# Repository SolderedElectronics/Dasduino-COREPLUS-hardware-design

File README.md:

# Dasduino COREPLUS Hardware Design

## About the Product

|  |
| :----------------------------------------------------------: |
| [Buy Dasduino COREPLUS](https://www.solde.red/333268) |

The soldered version of the ATmega2560 microcontroller board has arrived! It is designed for enthusiasts and professionals in the field of electronics and DIY projects. The heart of the board, the ATmega2560, is a powerful 8-bit microcontroller that offers enough processing power for demanding applications. The board comes with a large number of digital and analog inputs/outputs, allowing users to connect various sensors and actuators. The ATmega2560 contains a significant amount of Flash memory, SRAM, and EEPROM, which is sufficient for complex applications and data storage. The USB interface allows for easy programming and communication with a computer. It enables communication with various peripheral devices and modules using the qwiic system for simple connectivity. The board is compatible with popular development environments, such as Arduino IDE, which facilitates the development and implementation of projects.

This board is ideal for creating complex and versatile electronic projects, such as automatic systems, smart devices, robotics, and many others.

---

## Repository Contents

This repository contains all design files for Dasduino COREPLUS, organized as follows:

- **`CAD` folder**: Contains KiCAD design files, including:
  - Schematics
  - PCB layout
  - Panel PCB layout
  - Source 3D files in Fusion360, if any
  - All files are sorted by version with a detailed change log.
- **`OUTPUTS` folder**: Includes all production-ready files, such as:
  - Bill of Materials (BOM) and interactive BOM (iBOM)
  - PDF versions of schematics
  - 3D `.step` file of the board
  - 3D-printable models
  - Gerber files for PCB manufacturing
  - Image of the pinout of the board
  - Product image
  - Compliance, legal and generic sales documents

Refer to the `Change Log` in the CAD folder for details about updates between versions.

---

## Learn More About the Product

Beyond the repository, explore the following resources:

### Soldered Verify

The **Soldered Verify** system ensures every board you purchase from Soldered is fully functional. It also provides access to exclusive test data for your product. To get started, find the unique Soldered Verify ID on your product's packaging and enter the ID on the [Soldered Verify page](https://soldered.com/verify/) to access test results and additional product details.

### Soldered Community

Soldered Community is your go-to place for technical support. Our engineers track and answer all questions posted there, and it’s a great space for the maker community. Get answers to your questions and solutions for your challenges at [Soldered Community](https://soldered.com/community).

### solde.red

solde.red is an ultimate URL shortener and information hub. Access it by typing solde.red/ followed by your product SKU, e.g., [solde.red/333000](https://solde.red/333000), to find getting-started guides, datasheets, open-source hardware and software files, certifications, images, pinouts, and more. Read more about the shortener [here](https://solde.red/info/).

---

## Contributing

Contributions are welcome! Here’s how you can get involved:

- Submit pull requests to enhance the design or fix issues.
- Report bugs or problems by opening an issue.

We encourage community collaboration to make this product even better.

---

## About Soldered

[Soldered for Makers](https://soldered.com) specializes in designing and manufacturing electronic products tailored for enthusiasts, ranging from hobbyists to professionals. Our portfolio includes electronic boards, sensors, and actuators that are widely utilized in fields such as microelectronics, mechatronics, robotics, programming, and IoT. Every product we offer is designed in-house and built upon open-source hardware and software platforms. Proudly certified and manufactured within the European Union, our catalog likely includes the product you need for your project.

We complement these products with comprehensive tutorials and manuals, product descriptions, schematics, programming codes, and project examples. Our round-the-clock [customer and technical support](https://soldered.com/community) is available for all our products, irrespective of the sales channel. Soldered’s success and services reflect our maker community’s unwavering [trust](https://www.trustpilot.com/review/soldered.com), for which we are deeply grateful. Join our community and create using Soldered products.

---

## License

All Soldered open-source hardware (OSH) is under The TAPR Open Hardware License. Read more in the LICENSE file located in this repository.

**Disclaimer:**

No warranty - all designs in this repository are distributed in the hope that they will be useful, but without any warranty. They are provided "AS IS", therefore without warranty of any kind, either expressed or implied. The entire quality and performance of what you do with the contents of this repository are your responsibility. In no event Soldered Electronics will be liable for your damages, or losses, including any general, special, incidental, or consequential damage arising out of the use or inability to use the contents of this repository. 

---

## Have fun!

Thank you for your support from your fellow makers at Soldered Electronics.

Happy Making!

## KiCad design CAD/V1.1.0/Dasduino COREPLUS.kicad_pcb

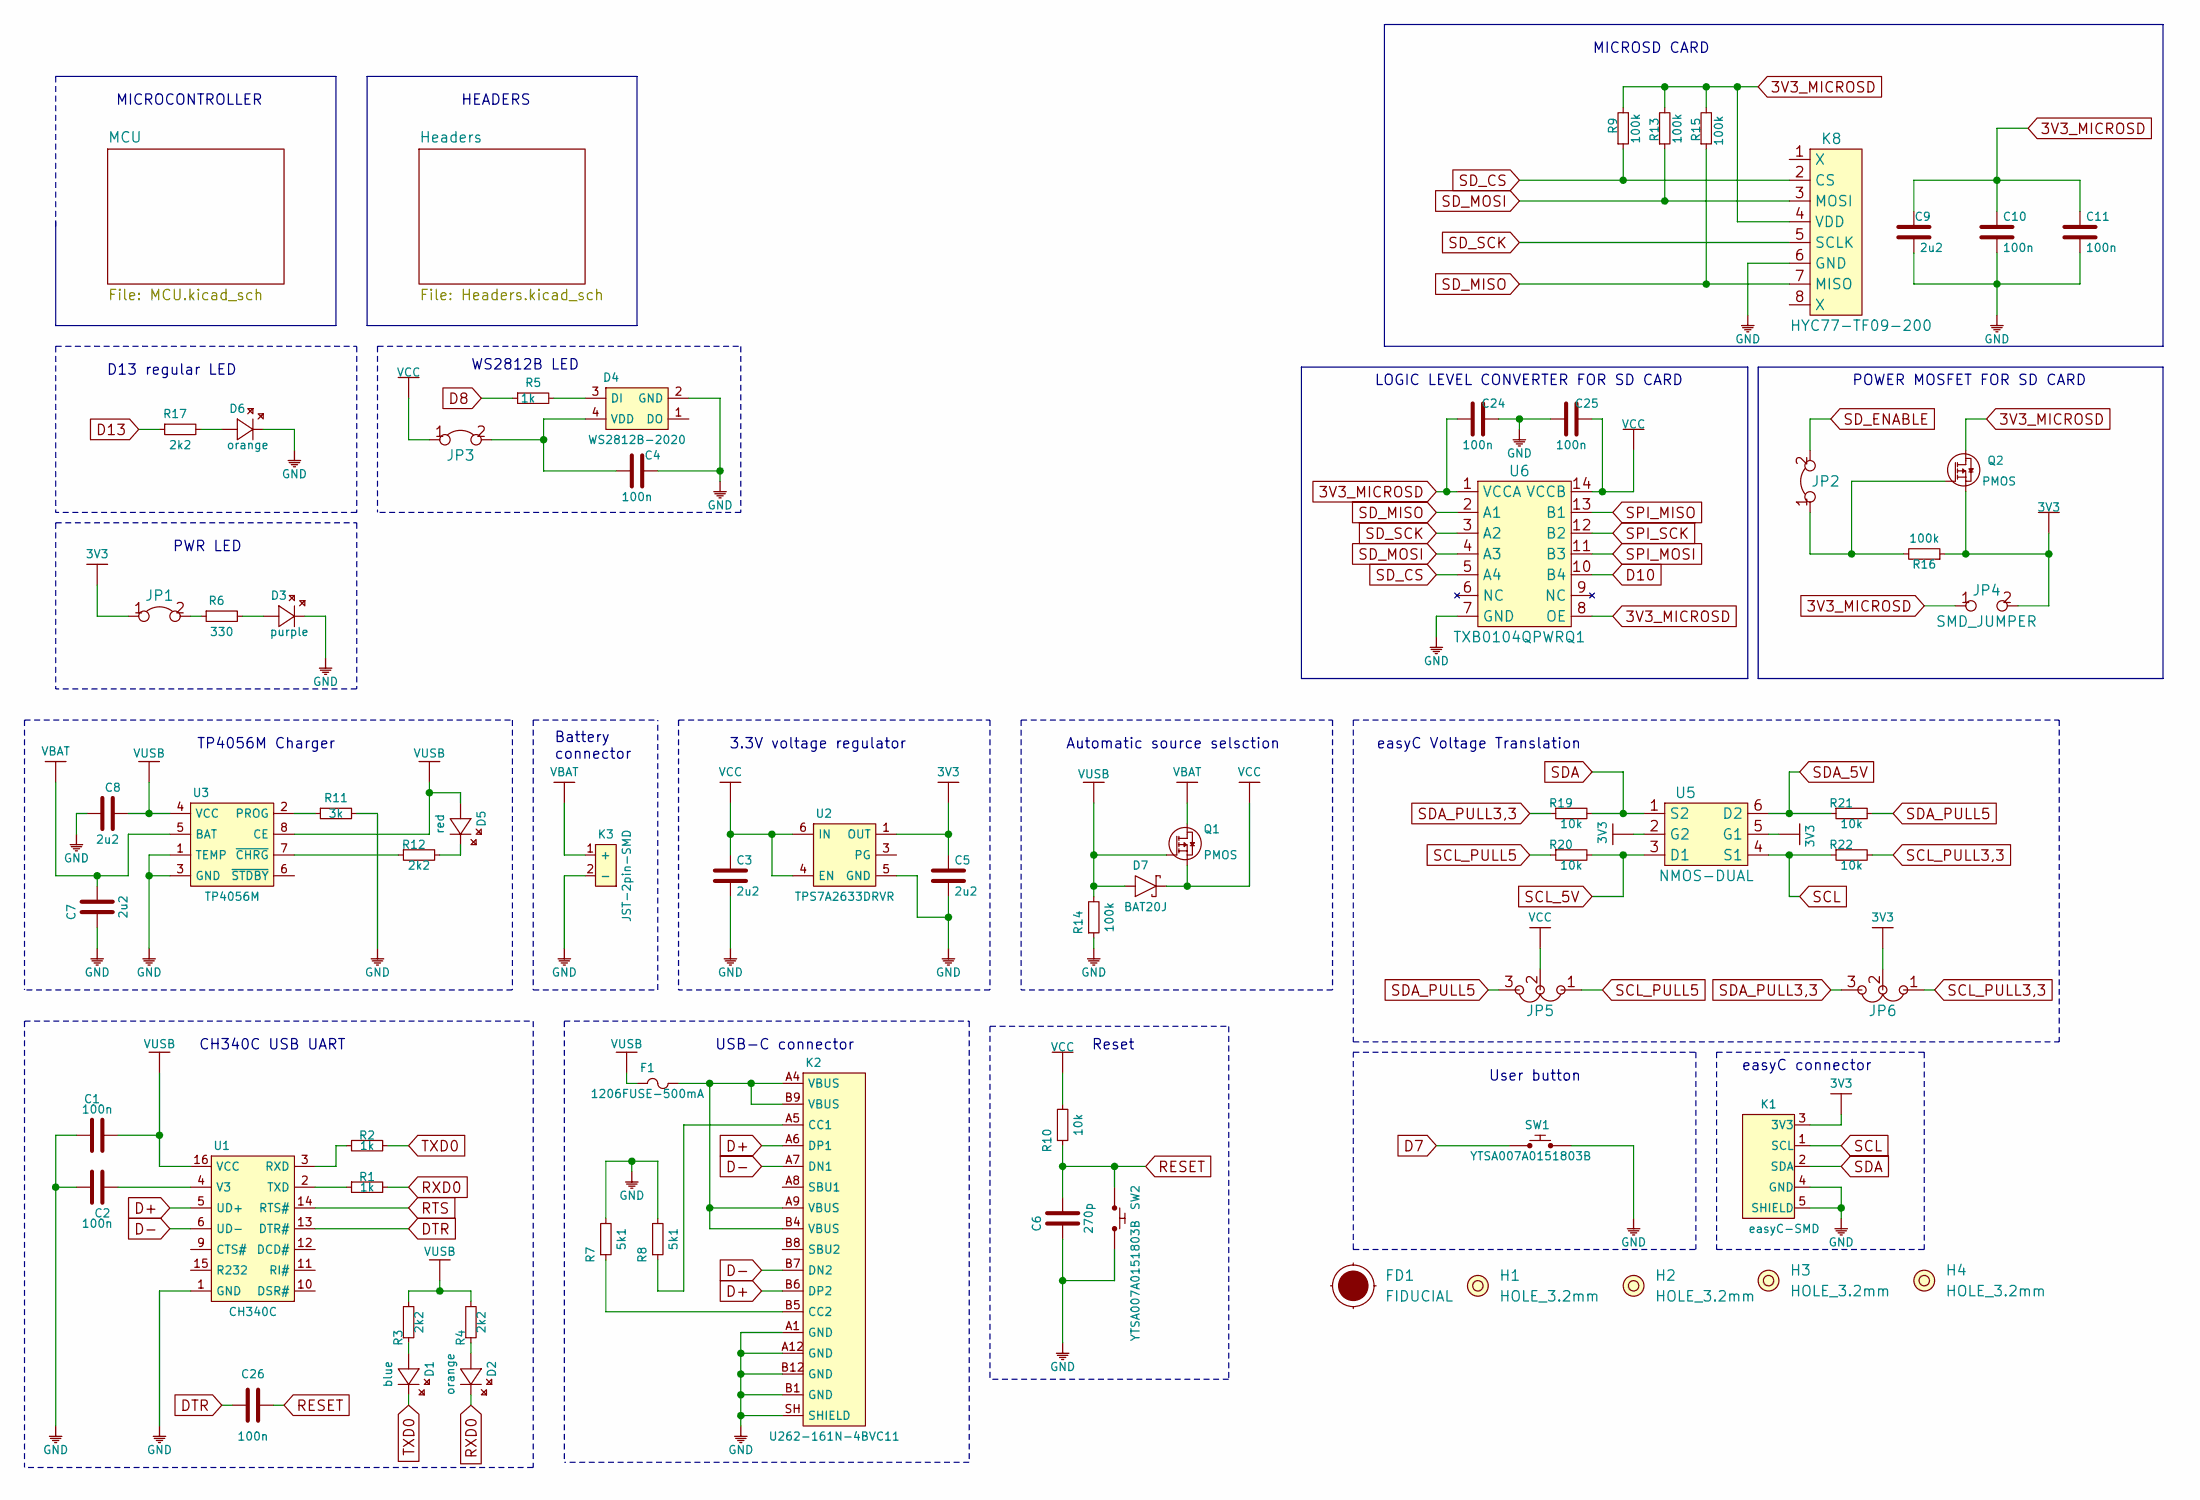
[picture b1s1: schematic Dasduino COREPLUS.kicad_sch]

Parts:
C1, C2, C4, C10, C11, C24, C25, C26: 100n; 0603C
C3, C5, C7, C8, C9: 2u2; 0603C
C6: 270p; 0603C
D1: blue; 0402LED
D2, D6: orange; 0402LED
D3: purple; 0402LED
D4: WS2812B-2020
D5: red; 0402LED
D7: BAT20J; SOD-323
F1: 1206FUSE-500mA; 1206FUSE
FD1: FIDUCIAL; FIDUCIAL_23
H1, H2, H3, H4: HOLE_3.2mm
JP1, JP2, JP3: SMD-JUMPER-CONNECTED_TRACE_SOLDERMASK
JP4: SMD_JUMPER
JP5, JP6: SMD_JUMPER_3_PAD_TRACE
K1: easyC-SMD; easyC-connector
K2: U262-161N-4BVC11
K3: JST-2pin-SMD
K8: HYC77-TF09-200
Q1, Q2: PMOS; SOT-23-3
R1, R2, R5: 1k; 0603R
R3, R4, R12, R17: 2k2; 0402R
R6: 330; 0402R
R7, R8: 5k1; 0603R
R9, R13, R14, R15, R16: 100k; 0603R
R10, R19, R20, R21, R22: 10k; 0603R
R11: 3k; 0603R
SW1, SW2: YTSA007A0151803B
U1: CH340C; SOP-16
U2: TPS7A2633DRVR
U3: TP4056M; TP4056M-MSOP8
U5: NMOS-DUAL; SOT-363
U6: TXB0104QPWRQ1

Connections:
3V3: C5.2, JP1.1, JP4.2, JP6.2, K1.3 (3V3), Q2.2 (S), R16.1, U2.1 (OUT), U5.2 (G2), U5.5 (G1); also elsewhere on the board
3V3_MICROSD: C9.2, C10.2, C11.2, C24.1, JP4.1, K8.4 (VDD), Q2.3 (D), R9.2, R13.2, R15.2, U6.1 (VCCA), U6.8 (OE)
D7: SW1.1; also elsewhere on the board
D8: R5.1; also elsewhere on the board
D10: U6.10 (B4); also elsewhere on the board
D13: R17.1; also elsewhere on the board
D+: K2.A6 (DP1), K2.B6 (DP2), U1.5 (UD+)
D-: K2.A7 (DN1), K2.B7 (DN2), U1.6 (UD-)
DTR: C26.2, U1.13 (DTR#)
GND: C1.1, C2.2, C3.1, C4.2, C5.1, C6.1, C7.1, C8.2, C9.1, C10.1, C11.1, C24.2, C25.1, D3.2 (K), D4.2 (GND), D6.2 (K), K1.4 (GND), K1.5 (SHIELD), K2.A1 (GND), K2.A12 (GND), K2.B1 (GND), K2.B12 (GND), K2.SH (SHIELD), K3.2 (-), K8.6 (GND), R7.2, R8.2, R11.2, R14.1, SW1.2, SW2.2, U1.1 (GND), U2.5 (GND), U3.1 (TEMP), U3.3 (GND), U6.7 (GND); also elsewhere on the board
unnamed: C2.1, U1.4 (V3)
unnamed: C4.1, D4.4 (VDD), JP3.2
unnamed: D1.1 (A), R3.1
unnamed: D2.1 (A), R4.1
unnamed: D3.1 (A), R6.2
unnamed: D4.3 (DI), R5.2
unnamed: D5.2 (K), R12.2
unnamed: D6.1 (A), R17.2
unnamed: F1.2, K2.A4 (VBUS), K2.A9 (VBUS), K2.B4 (VBUS), K2.B9 (VBUS)
unnamed: JP1.2, R6.1
unnamed: JP2.1, Q2.1 (G), R16.2
unnamed: K2.A5 (CC1), R8.1
unnamed: K2.B5 (CC2), R7.1
unnamed: R1.1, U1.2 (TXD)
unnamed: R2.1, U1.3 (RXD)
unnamed: R11.1, U3.2 (PROG)
unnamed: R12.1, U3.7 (~CHRG)
RESET: C6.2, C26.1, R10.1, SW2.1; also elsewhere on the board
RTS: U1.14 (RTS#)
RXD0: D2.2 (K), R1.2; also elsewhere on the board
SCL: K1.1 (SCL), R22.1, U5.4 (S1)
SCL_5V: R20.2, U5.3 (D1); also elsewhere on the board
SCL_PULL3,3: JP6.1, R22.2
SCL_PULL5: JP5.1, R20.1
SDA: K1.2 (SDA), R19.2, U5.1 (S2)
SDA_5V: R21.1, U5.6 (D2); also elsewhere on the board
SDA_PULL3,3: JP6.3, R19.1
SDA_PULL5: JP5.3, R21.2
SD_CS: K8.2 (CS), R9.1, U6.5 (A4)
SD_ENABLE: JP2.2; also elsewhere on the board
SD_MISO: K8.7 (MISO), R15.1, U6.2 (A1)
SD_MOSI: K8.3 (MOSI), R13.1, U6.4 (A3)
SD_SCK: K8.5 (SCLK), U6.3 (A2)
SPI_MISO: U6.13 (B1); also elsewhere on the board
SPI_MOSI: U6.11 (B3); also elsewhere on the board
SPI_SCK: U6.12 (B2); also elsewhere on the board
TXD0: D1.2 (K), R2.2; also elsewhere on the board
VBAT: C7.2, K3.1 (+), Q1.3 (D), U3.5 (BAT); also elsewhere on the board
VCC: C3.2, C25.2, D7.2 (C), JP3.1, JP5.2, Q1.2 (S), R10.2, U2.4 (EN), U2.6 (IN), U6.14 (VCCB); also elsewhere on the board
VUSB: C1.2, C8.1, D5.1 (A), D7.1 (A), F1.1, Q1.1 (G), R3.2, R4.2, R14.2, U1.16 (VCC), U3.4 (VCC), U3.8 (CE)

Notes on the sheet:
MICROSD CARD
TP4056M Charger
PWR LED
easyC Voltage Translation
LOGIC LEVEL CONVERTER FOR SD CARD
3.3V voltage regulator
easyC connector
CH340C USB UART
User button
USB-C connector
WS2812B LED
MICROCONTROLLER
D13 regular LED
HEADERS
Battery connector
POWER MOSFET FOR SD CARD
Reset
Automatic source selsction

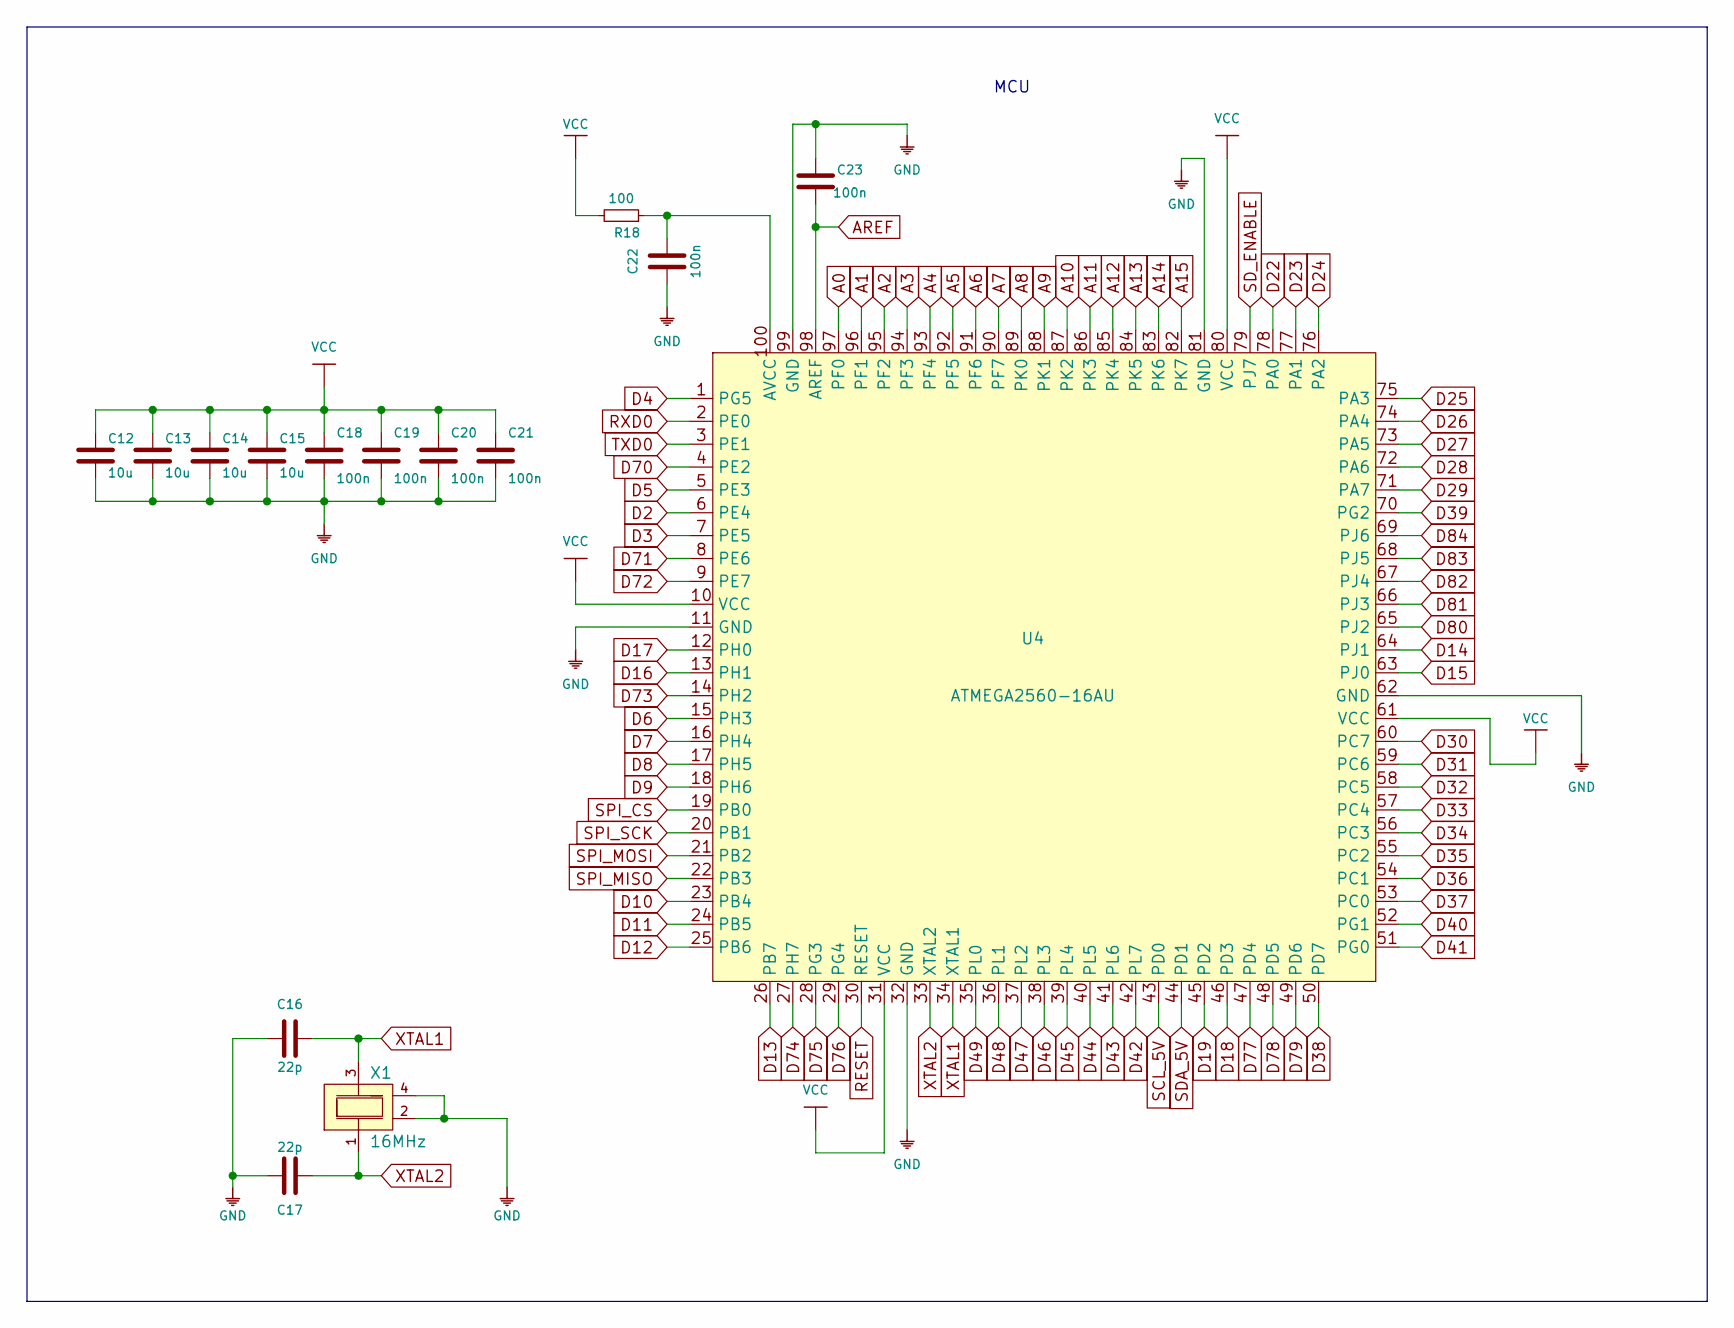
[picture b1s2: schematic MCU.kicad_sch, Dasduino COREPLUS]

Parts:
C12, C13, C14, C15: 10u; 1206C
C16, C17: 22p; 0603C
C18, C19, C20, C21, C22, C23: 100n; 0603C
R18: 100; 0603R
U4: ATMEGA2560-16AU; TQFP-100
X1: 16MHz; CRYSTAL_3225__4_PAD

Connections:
A0: U4.97 (PF0); also elsewhere on the board
A1: U4.96 (PF1); also elsewhere on the board
A2: U4.95 (PF2); also elsewhere on the board
A3: U4.94 (PF3); also elsewhere on the board
A4: U4.93 (PF4); also elsewhere on the board
A5: U4.92 (PF5); also elsewhere on the board
A6: U4.91 (PF6); also elsewhere on the board
A7: U4.90 (PF7); also elsewhere on the board
A8: U4.89 (PK0); also elsewhere on the board
A9: U4.88 (PK1); also elsewhere on the board
A10: U4.87 (PK2); also elsewhere on the board
A11: U4.86 (PK3); also elsewhere on the board
A12: U4.85 (PK4); also elsewhere on the board
A13: U4.84 (PK5); also elsewhere on the board
A14: U4.83 (PK6); also elsewhere on the board
A15: U4.82 (PK7); also elsewhere on the board
AREF: C23.1, U4.98 (AREF); also elsewhere on the board
D2: U4.6 (PE4); also elsewhere on the board
D3: U4.7 (PE5); also elsewhere on the board
D4: U4.1 (PG5); also elsewhere on the board
D5: U4.5 (PE3); also elsewhere on the board
D6: U4.15 (PH3); also elsewhere on the board
D7: U4.16 (PH4); also elsewhere on the board
D8: U4.17 (PH5); also elsewhere on the board
D9: U4.18 (PH6); also elsewhere on the board
D10: U4.23 (PB4); also elsewhere on the board
D11: U4.24 (PB5); also elsewhere on the board
D12: U4.25 (PB6); also elsewhere on the board
D13: U4.26 (PB7); also elsewhere on the board
D14: U4.64 (PJ1); also elsewhere on the board
D15: U4.63 (PJ0); also elsewhere on the board
D16: U4.13 (PH1); also elsewhere on the board
D17: U4.12 (PH0); also elsewhere on the board
D18: U4.46 (PD3); also elsewhere on the board
D19: U4.45 (PD2); also elsewhere on the board
D22: U4.78 (PA0); also elsewhere on the board
D23: U4.77 (PA1); also elsewhere on the board
D24: U4.76 (PA2); also elsewhere on the board
D25: U4.75 (PA3); also elsewhere on the board
D26: U4.74 (PA4); also elsewhere on the board
D27: U4.73 (PA5); also elsewhere on the board
D28: U4.72 (PA6); also elsewhere on the board
D29: U4.71 (PA7); also elsewhere on the board
D30: U4.60 (PC7); also elsewhere on the board
D31: U4.59 (PC6); also elsewhere on the board
D32: U4.58 (PC5); also elsewhere on the board
D33: U4.57 (PC4); also elsewhere on the board
D34: U4.56 (PC3); also elsewhere on the board
D35: U4.55 (PC2); also elsewhere on the board
D36: U4.54 (PC1); also elsewhere on the board
D37: U4.53 (PC0); also elsewhere on the board
D38: U4.50 (PD7); also elsewhere on the board
D39: U4.70 (PG2); also elsewhere on the board
D40: U4.52 (PG1); also elsewhere on the board
D41: U4.51 (PG0); also elsewhere on the board
D42: U4.42 (PL7); also elsewhere on the board
D43: U4.41 (PL6); also elsewhere on the board
D44: U4.40 (PL5); also elsewhere on the board
D45: U4.39 (PL4); also elsewhere on the board
D46: U4.38 (PL3); also elsewhere on the board
D47: U4.37 (PL2); also elsewhere on the board
D48: U4.36 (PL1); also elsewhere on the board
D49: U4.35 (PL0); also elsewhere on the board
D70: U4.4 (PE2); also elsewhere on the board
D71: U4.8 (PE6); also elsewhere on the board
D72: U4.9 (PE7); also elsewhere on the board
D73: U4.14 (PH2); also elsewhere on the board
D74: U4.27 (PH7); also elsewhere on the board
D75: U4.28 (PG3); also elsewhere on the board
D76: U4.29 (PG4); also elsewhere on the board
D77: U4.47 (PD4); also elsewhere on the board
D78: U4.48 (PD5); also elsewhere on the board
D79: U4.49 (PD6); also elsewhere on the board
D80: U4.65 (PJ2); also elsewhere on the board
D81: U4.66 (PJ3); also elsewhere on the board
D82: U4.67 (PJ4); also elsewhere on the board
D83: U4.68 (PJ5); also elsewhere on the board
D84: U4.69 (PJ6); also elsewhere on the board
GND: C12.1, C13.1, C14.1, C15.1, C16.1, C17.2, C18.1, C19.1, C20.1, C21.1, C22.1, C23.2, U4.11 (GND), U4.32 (GND), U4.62 (GND), U4.81 (GND), U4.99 (GND), X1.2, X1.4; also elsewhere on the board
unnamed: C22.2, R18.1, U4.100 (AVCC)
RESET: U4.30 (RESET); also elsewhere on the board
RXD0: U4.2 (PE0); also elsewhere on the board
SCL_5V: U4.43 (PD0); also elsewhere on the board
SDA_5V: U4.44 (PD1); also elsewhere on the board
SD_ENABLE: U4.79 (PJ7); also elsewhere on the board
SPI_CS: U4.19 (PB0); also elsewhere on the board
SPI_MISO: U4.22 (PB3); also elsewhere on the board
SPI_MOSI: U4.21 (PB2); also elsewhere on the board
SPI_SCK: U4.20 (PB1); also elsewhere on the board
TXD0: U4.3 (PE1); also elsewhere on the board
VCC: C12.2, C13.2, C14.2, C15.2, C18.2, C19.2, C20.2, C21.2, R18.2, U4.10 (VCC), U4.31 (VCC), U4.61 (VCC), U4.80 (VCC); also elsewhere on the board
XTAL1: C16.2, U4.34 (XTAL1), X1.3
XTAL2: C17.1, U4.33 (XTAL2), X1.1

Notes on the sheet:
MCU

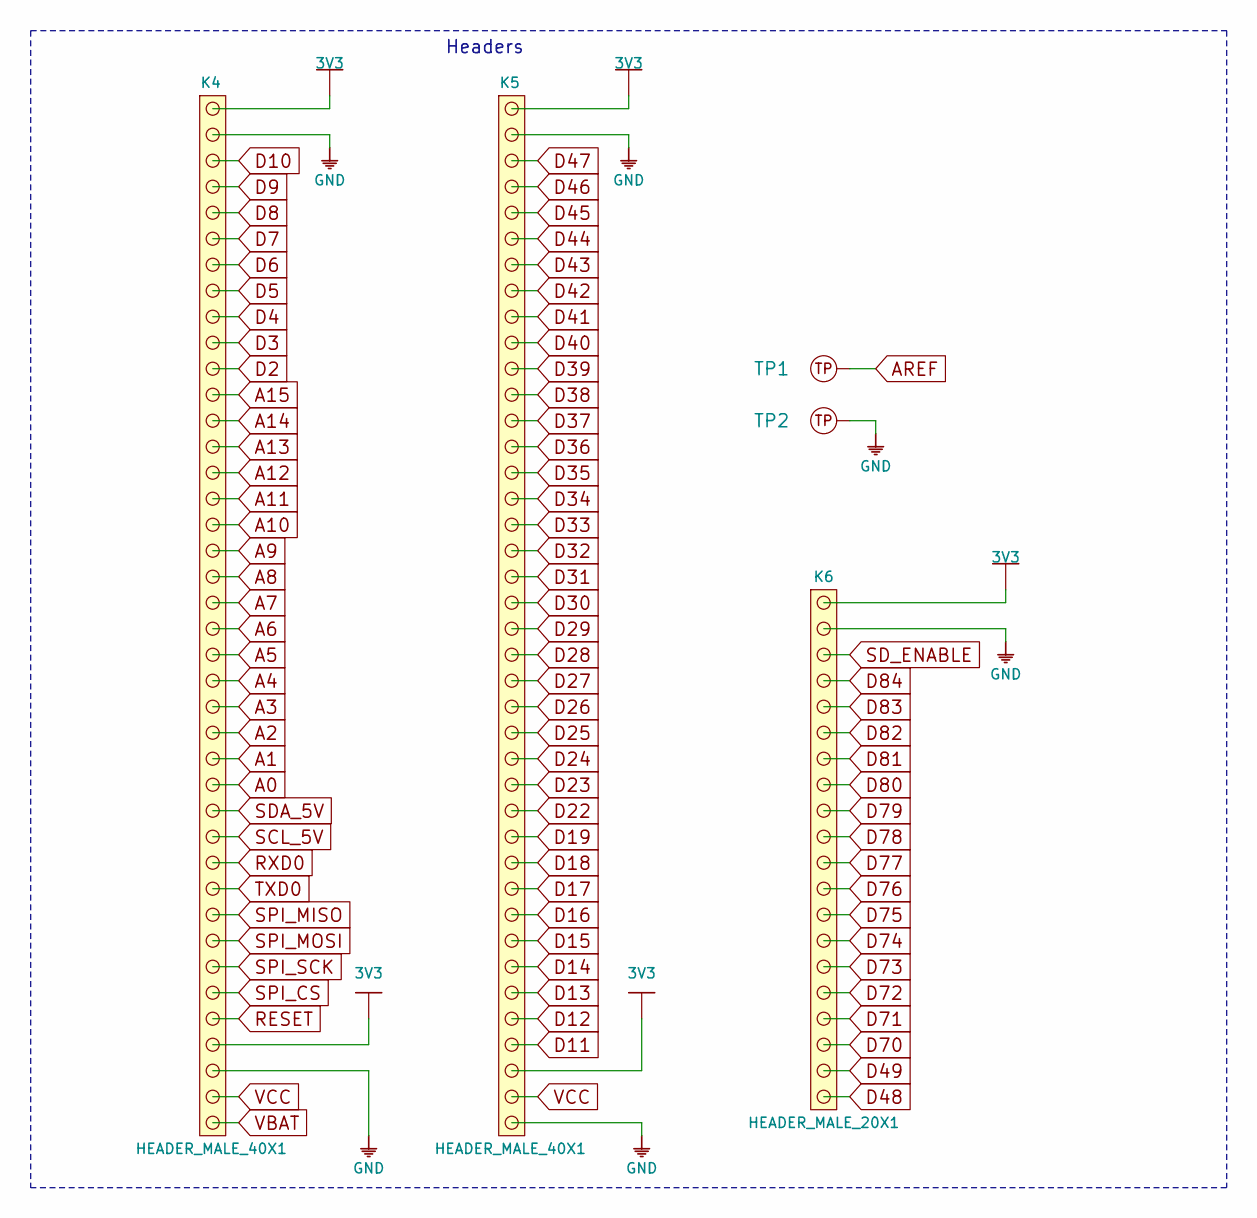
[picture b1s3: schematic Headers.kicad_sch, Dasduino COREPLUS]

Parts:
K4, K5: HEADER_MALE_40X1
K6: HEADER_MALE_20X1; HEADER_MALE_20x1
TP1, TP2: Test_Point_SMD_0.8mm

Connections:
3V3: K4.1, K4.37, K5.1, K5.38, K6.20; also elsewhere on the board
A0: K4.27; also elsewhere on the board
A1: K4.26; also elsewhere on the board
A2: K4.25; also elsewhere on the board
A3: K4.24; also elsewhere on the board
A4: K4.23; also elsewhere on the board
A5: K4.22; also elsewhere on the board
A6: K4.21; also elsewhere on the board
A7: K4.20; also elsewhere on the board
A8: K4.19; also elsewhere on the board
A9: K4.18; also elsewhere on the board
A10: K4.17; also elsewhere on the board
A11: K4.16; also elsewhere on the board
A12: K4.15; also elsewhere on the board
A13: K4.14; also elsewhere on the board
A14: K4.13; also elsewhere on the board
A15: K4.12; also elsewhere on the board
AREF: TP1.TP; also elsewhere on the board
D2: K4.11; also elsewhere on the board
D3: K4.10; also elsewhere on the board
D4: K4.9; also elsewhere on the board
D5: K4.8; also elsewhere on the board
D6: K4.7; also elsewhere on the board
D7: K4.6; also elsewhere on the board
D8: K4.5; also elsewhere on the board
D9: K4.4; also elsewhere on the board
D10: K4.3; also elsewhere on the board
D11: K5.37; also elsewhere on the board
D12: K5.36; also elsewhere on the board
D13: K5.35; also elsewhere on the board
D14: K5.34; also elsewhere on the board
D15: K5.33; also elsewhere on the board
D16: K5.32; also elsewhere on the board
D17: K5.31; also elsewhere on the board
D18: K5.30; also elsewhere on the board
D19: K5.29; also elsewhere on the board
D22: K5.28; also elsewhere on the board
D23: K5.27; also elsewhere on the board
D24: K5.26; also elsewhere on the board
D25: K5.25; also elsewhere on the board
D26: K5.24; also elsewhere on the board
D27: K5.23; also elsewhere on the board
D28: K5.22; also elsewhere on the board
D29: K5.21; also elsewhere on the board
D30: K5.20; also elsewhere on the board
D31: K5.19; also elsewhere on the board
D32: K5.18; also elsewhere on the board
D33: K5.17; also elsewhere on the board
D34: K5.16; also elsewhere on the board
D35: K5.15; also elsewhere on the board
D36: K5.14; also elsewhere on the board
D37: K5.13; also elsewhere on the board
D38: K5.12; also elsewhere on the board
D39: K5.11; also elsewhere on the board
D40: K5.10; also elsewhere on the board
D41: K5.9; also elsewhere on the board
D42: K5.8; also elsewhere on the board
D43: K5.7; also elsewhere on the board
D44: K5.6; also elsewhere on the board
D45: K5.5; also elsewhere on the board
D46: K5.4; also elsewhere on the board
D47: K5.3; also elsewhere on the board
D48: K6.1; also elsewhere on the board
D49: K6.2; also elsewhere on the board
D70: K6.3; also elsewhere on the board
D71: K6.4; also elsewhere on the board
D72: K6.5; also elsewhere on the board
D73: K6.6; also elsewhere on the board
D74: K6.7; also elsewhere on the board
D75: K6.8; also elsewhere on the board
D76: K6.9; also elsewhere on the board
D77: K6.10; also elsewhere on the board
D78: K6.11; also elsewhere on the board
D79: K6.12; also elsewhere on the board
D80: K6.13; also elsewhere on the board
D81: K6.14; also elsewhere on the board
D82: K6.15; also elsewhere on the board
D83: K6.16; also elsewhere on the board
D84: K6.17; also elsewhere on the board
GND: K4.2, K4.38, K5.2, K5.40, K6.19, TP2.TP; also elsewhere on the board
RESET: K4.36; also elsewhere on the board
RXD0: K4.30; also elsewhere on the board
SCL_5V: K4.29; also elsewhere on the board
SDA_5V: K4.28; also elsewhere on the board
SD_ENABLE: K6.18; also elsewhere on the board
SPI_CS: K4.35; also elsewhere on the board
SPI_MISO: K4.32; also elsewhere on the board
SPI_MOSI: K4.33; also elsewhere on the board
SPI_SCK: K4.34; also elsewhere on the board
TXD0: K4.31; also elsewhere on the board
VBAT: K4.40; also elsewhere on the board
VCC: K4.39, K5.39; also elsewhere on the board

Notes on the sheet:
Headers
